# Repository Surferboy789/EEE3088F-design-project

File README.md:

# EEE3088F-design-project
Collaborative space for EEE3088F design project

Hi guys, try edit this file to make sure you have been added as a collaborator correctly. Thanks

Leoma edited
Matt testing git pull and push

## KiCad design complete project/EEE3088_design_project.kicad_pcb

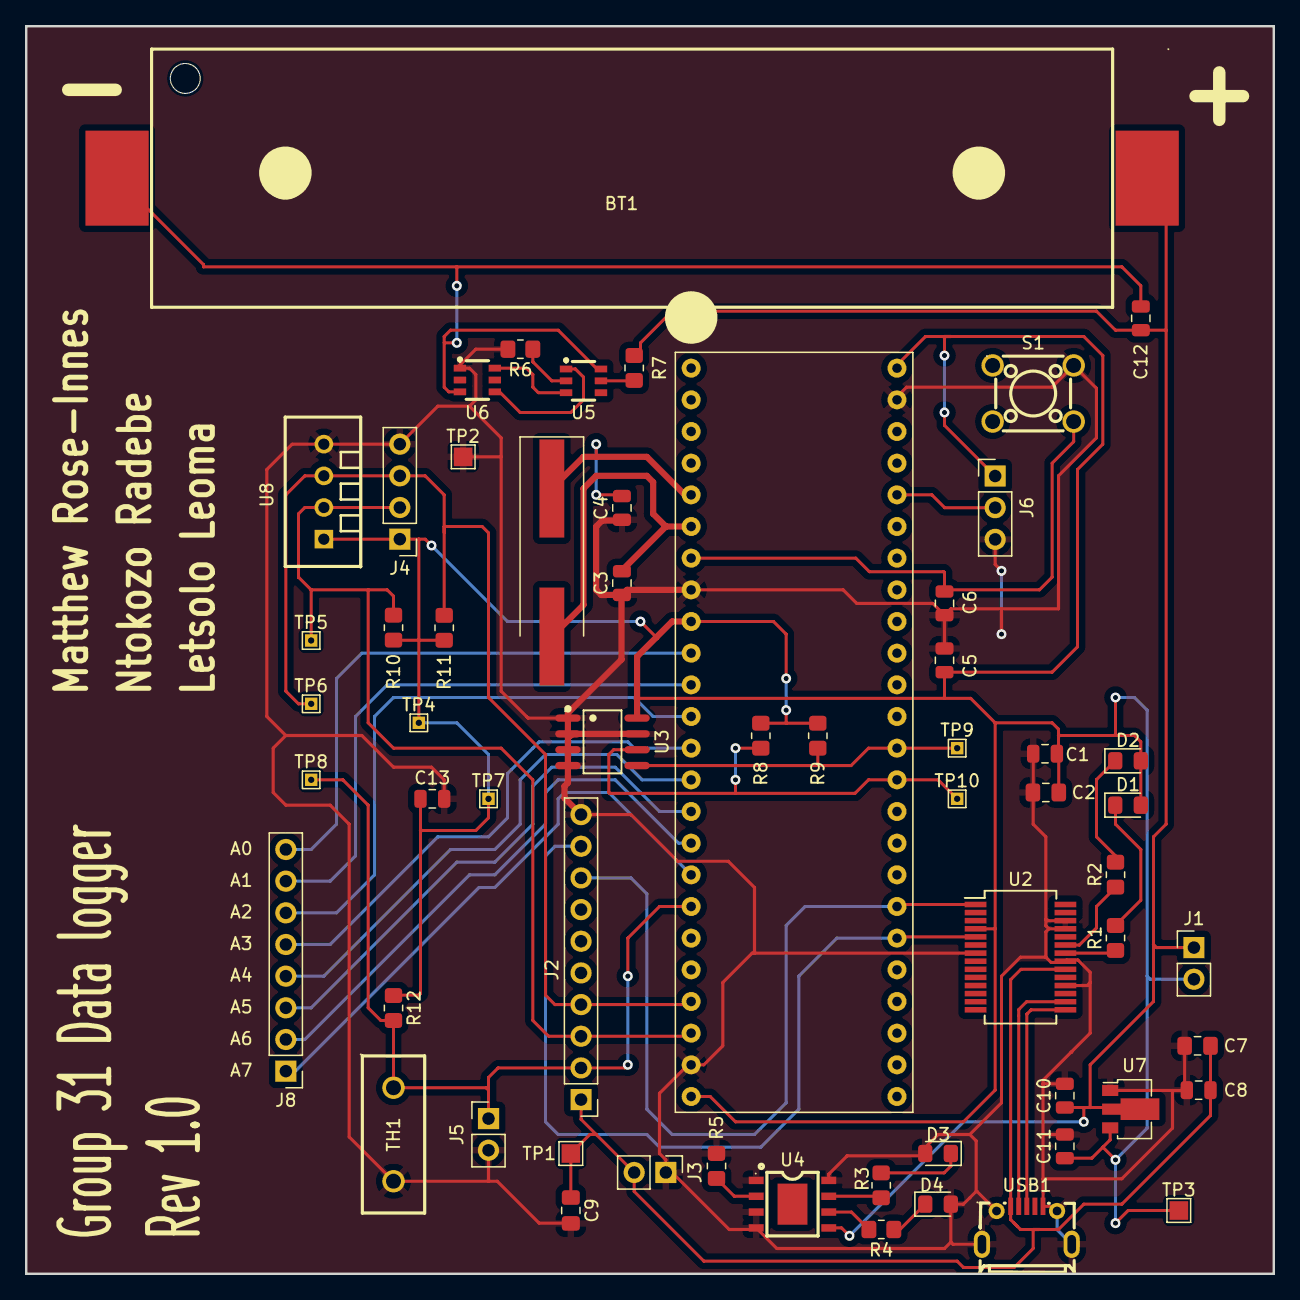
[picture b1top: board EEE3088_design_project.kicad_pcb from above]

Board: 2 copper layers, 100.1 x 100.1 mm, 59 parts (0 on the bottom side), 39 nets.

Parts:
BT1: Battery_Cell; BATTERY holder
C1, C12: 10nF; C_0805_2012Metric
C2: 1uF; C_0805_2012Metric_Pad1.18x1.45mm_HandSolder
C3, C4: 20pF; C_0805_2012Metric
C5, C6, C8: 100nF; C_0805_2012Metric
C7, C9: 10uF; C_0805_2012Metric_Pad1.18x1.45mm_HandSolder
C10, C11: 10uF; C_0805_2012Metric
C13: 100n; C_0805_2012Metric
D1, D2: LED; LED_0805_2012Metric_Pad1.15x1.40mm_HandSolder
D3: RED LED; LED_0805_2012Metric_Pad1.15x1.40mm_HandSolder
D4: GREEN LED; LED_0805_2012Metric_Pad1.15x1.40mm_HandSolder
J1, J3: Conn_01x02_Male; PinHeader_1x02_P2.54mm_Vertical
J2: Conn_01x10_Pin; PinHeader_1x10_P2.54mm_Vertical
J4: Conn_01x04_Pin; PinHeader_1x04_P2.54mm_Vertical
J5: Conn_01x02_Pin; PinHeader_1x02_P2.54mm_Vertical
J6: Conn_01x03_Pin; PinHeader_1x03_P2.54mm_Vertical
J7: Conn_02x24_Counter_Clockwise; STM32F051C6T6
J8: Conn_01x08_Pin; PinHeader_1x08_P2.54mm_Vertical
R1, R2: 330R; R_0805_2012Metric_Pad1.20x1.40mm_HandSolder
R3, R4: 1K; R_0805_2012Metric_Pad1.20x1.40mm_HandSolder
R5, R6: 1k; R_0805_2012Metric_Pad1.20x1.40mm_HandSolder
R7: 500; R_0805_2012Metric_Pad1.20x1.40mm_HandSolder
R8, R9: 4K7; R_0805_2012Metric_Pad1.20x1.40mm_HandSolder
R10, R11: 4.7k; R_0805_2012Metric_Pad1.20x1.40mm_HandSolder
R12: 5k; R_0805_2012Metric_Pad1.20x1.40mm_HandSolder
S1: C13828; SW-TH_4P-L6.0-W6.0-P4.50-LS6.5
TH1: Thermistor; RES-TH_L12.5-W5.0-P7.50-D0.7
TP1: TestPoint; TestPoint_Pad_1.5x1.5mm
TP2: GND; TestPoint_Pad_1.5x1.5mm
TP3: 3.3V; TestPoint_Pad_1.5x1.5mm
TP4: TestPoint; TestPoint_THTPad_1.0x1.0mm_Drill0.5mm
TP5: Temp SDA; TestPoint_THTPad_1.0x1.0mm_Drill0.5mm
TP6: Temp SLC; TestPoint_THTPad_1.0x1.0mm_Drill0.5mm
TP7: V3.3; TestPoint_THTPad_1.0x1.0mm_Drill0.5mm
TP8: Analog sens; TestPoint_THTPad_1.0x1.0mm_Drill0.5mm
TP9: Eprom SDA; TestPoint_THTPad_1.0x1.0mm_Drill0.5mm
TP10: Eprom SLC; TestPoint_THTPad_1.0x1.0mm_Drill0.5mm
U2: FT232RL; SSOP-28_5.3x10.2mm_P0.65mm
U3: AT24C256C-SSHL-T; SOIC-8_L4.9-W3.9-P1.27-LS6.0-BL
U4: TP4056; ESOP-8_L4.9-W3.9-P1.27-LS6.0-BL-EP
U5: DW01A-G; SOT-23
U6: FS8205A_C908265; SOT-23-6_L2.9-W1.6-P0.95-LS2.8-BR
U7: HT75xx-1-SOT89; SOT-89-3
U8: DHT22; SENSOR-TH_HAIGU_DHT22
USB1: MICROXNJ; MICRO-USB-SMD_MICROXNJ
Y1: 8MHz; Crystal_SMD_HC49-SD_HandSoldering

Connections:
5V: C7.2, C8.2, C9.1, J2.1, J3.2, TP1.1, U2.20 (VCC), USB1.1 (VBUS)
/Microcontroller Interface/D+: U2.15 (USBD+), USB1.3 (D+)
/Microcontroller Interface/D-: U2.16 (USBD-), USB1.2 (D-)
/Microcontroller Interface/Eprom_SDA: J7.36, R9.1, TP9.1, U3.5 (SDA)
/Microcontroller Interface/Eprom_SLC: J7.35, R8.1, TP10.1, U3.6 (SCL)
/Microcontroller Interface/NRST: C6.2, J7.7, S1.4
/Microcontroller Interface/RX: J2.9, J7.30, U2.5 (RXD)
/Microcontroller Interface/TX: J2.8, J7.31, U2.1 (TXD)
/Power managment/OC: U5.3 (OC), U6.6 (G1)
/Power managment/OD: U5.1 (OD), U6.4 (G2)
/Power managment/POS_terminal: BT1.1 (+), C10.1, C12.1, J1.1, R7.1, U4.5 (BAT), U7.2 (VIN)
Analog temp sensor: J2.2, J5.1, J7.18, R12.2, TH1.1, TP8.1
GND: C1.1, C2.1, C3.1, C4.1, C5.1, C6.1, C7.1, C8.1, C9.2, C10.2, C11.2, C13.2, D3.2 (A), D4.2 (A), J2.10, J3.1, J4.4, J5.2, J6.3, J7.8, J7.23, J7.47, R5.2, R6.2, S1.2, TH1.2, TP2.1, U2.7 (GND), U2.18 (GND), U2.21 (GND), U2.25 (AGND), U2.26 (TEST), U3.1 (A0), U3.2 (A1), U3.3 (A2), U3.4 (GND), U3.7 (WP), U4.1 (TEMP), U4.3 (GND), U4.4 (VCC), U4.8 (CE), U6.1 (S1), U7.1 (GND), U8.4 (GND), USB1.5 (GND), USB1.6 (SH1), USB1.7 (SH2), USB1.8 (SH3), USB1.9 (SH4)
unnamed: BT1.2 (-), C12.2, U5.6 (GND), U6.3 (S2)
unnamed: D1.1 (K), R1.2
unnamed: D2.1 (K), R2.2
unnamed: D3.1 (K), R3.1
unnamed: D4.1 (K), R4.1
unnamed: J6.2, J7.44
unnamed: C4.2, J7.5, Y1.1
unnamed: C3.2, J7.6, Y1.2
unnamed: R2.1, U2.23 (CBUS0)
unnamed: R1.1, U2.22 (CBUS1)
unnamed: R3.2, U4.7 (CHRG#)
unnamed: R5.1, U4.2 (PROG)
unnamed: R4.2, U4.6 (STDBY#)
unnamed: R6.1, U5.2 (CS)
unnamed: R7.2, U5.5 (VCC)
PA0: J7.10, J8.8
PA1: J7.11, J8.7
PA2: J7.12, J8.6
PA3: J7.13, J8.5
PA4: J7.14, J8.4
PA5: J7.15, J8.3
PA6: J7.16, J8.2
PA7: J7.17, J8.1
Temp_Sensor_SDA: J2.3, J4.2, J7.22, R10.2, TP5.1, U8.2 (SDA)
Temp_Sensor_SLC: J2.4, J4.3, J7.21, R11.2, TP6.1, U8.3 (SCK)
Vout3: C1.2, C2.2, C5.2, C11.1, C13.1, D1.2 (A), D2.2 (A), J1.2, J4.1, J6.1, J7.9, J7.24, J7.48, R8.2, R9.2, R10.1, R11.1, R12.1, TP3.1, TP4.1, TP7.1, U2.4 (VCCIO), U3.8 (VCC), U7.3 (VOUT), U8.1 (VDD)

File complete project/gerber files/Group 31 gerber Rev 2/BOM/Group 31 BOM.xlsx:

REFERENCE | VALUE | Extended Part | JLCPCB part no: | populate | Package | Price per unit | Total Price | Quantity
BT1 | Battery_Cell |  |  |  |  |  |  | 1
C9-C11 | 10uF | 0 | C15850 | Yes | .0805 | $0.0135 | $0.0405 | 3
C12 | 10nF | 0 | C57112 | Yes | .0603 | $0.0013 | $0.0013 | 1
D3 | RED LED | 0 | C2286 | Yes | LED_0603 | $0.0054 | $0.0054 | 1
D4 | GREEN LED | 0 | C2297 | Yes | .0805 | $0.0133 | $0.0133 | 1
U5 | DW01A-G | 1 | C61503 | Yes | SOT-23-6 | $0.1461 | $0.1461 | 1
J1, J3 | Conn_01x02_Male |  |  | no |  |  |  | 2
U6 | FS8205A | 1 | C908265 | yes | SOT-23-6 | $0.0552 | $0.0552 | 1
R3, R4, R5, R6 | 1K | 0 | C17414 | yes | 805 | 1E-3 | 4.0000000000000001E-3 | 3
7 | 500R | 0 | C17470 | yes | .0805 | 1.8E-3 | 1.8E-3 | 1
TP1, TP2 | TestPoint |  |  | no |  |  |  | 2
U7 | HT75xx-1-SOT89 | 0 | C14289 | yes | SOT-89-3 | $0.1315 | $0.1315 | 1
U4 | TP4056 | 0 | C16581 | yes | ESOP-8 | $0.2064 | $0.2064 | 1
C1 | 10nF | 0 | C49678 | yes | 805 | 4.5999999999999999E-3 | 4.5999999999999999E-3 | 1
C2 | 1uF | 0 | C28323 | yes | 805 | 8.6999999999999994E-3 | 8.6999999999999994E-3 | 1
C3, C4 | 20pF | 0 | C107145 | yes | 805 | 5.8999999999999999E-3 | 1.18E-2 | 2
C5, C6, C8 | 100nF | 0 | C49678 | yes | 805 | 4.5999999999999999E-3 | 1.38E-2 | 3
C7 | 10uF | 0 | C15850 | yes | 805 | 1.35E-2 | 1.35E-2 | 1
D1, D2 | LED | 0 | C2296 | yes | 805 | 1.1900000000000001E-2 | 3.9800000000000002E-2 | 2
J1 | USB_B_Micro | 1 | C404969 | yes | SMD | 3.3300000000000003E-2 | 3.0333000000000001 | 1
J2 | Conn_01x10_Pin |  |  | no |  |  |  | 1
R1, R2 | 330R | 0 | C17630 | yes | 805 | 1.6999999999999999E-3 | 3.3999999999999998E-3 | 2
SW1 | SW_Push | 1 | C13828 | yes | Through hole | 4.2500000000000003E-2 | 4.2500000000000003E-2 | 1
U1 | STM32 pin header |  |  | no |  |  |  | 1
U2 | FT232RL | 1 | C8690 | yes | SMD | 5.6292999999999997 | 8.6293000000000006 | 1
U3 | CAT24C256 | 0 | C6482 | yes | SOIC-8 | 0.53 | 0.53 | 1
R8, R9 | 4K7 | 0 | C17673 | yes | 805 | 1.6999999999999999E-3 | 3.3999999999999998E-3
J6 | Header |  |  | no
J8 | Header |  |  | no
Y1 | 8MHz | 0 | C12674 | yes | SMD | 8.6400000000000005E-2 | 8.6400000000000005E-2 | 1
C13 | 100nF | 0 | C49678 | yes | 805 | 4.5999999999999999E-3 | 4.5999999999999999E-3
R10, R11 | 4K7 | 0 | C17673 | yes | 805 | 1.6999999999999999E-3 | 3.3999999999999998E-3
J4 | Header |  |  | no
J5 | Header |  |  | no
TH1 | Thermistor | 1 | C190085 | yes | Through hole | $0.0353 | $0.0353
R12 | 5k | 0 | C784215 | yes | 805 | 2E-3 | 2E-3
U8 | DHT22 | 1 | C2880291 | yes | plugin | 1.4418 | 1.4418
 |  |  |  |  |  | Total cost | 13.878099999999998

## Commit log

2023-03-05 microcontroller files
2023-03-05 Assignment 2 microcontroller sub-module complete
2023-03-06 Create Power Management Submodule
2023-03-06 Create BOM
2023-03-13 assignment wk4 update
2023-03-14 Added Updated BOM
2023-03-14 added power managment
2023-03-20 added PCB files
2023-03-20 Changed directory of final project
2023-03-20 Latest update of PCB
2023-03-21 added BOM
2023-03-21 Updated Sensor Submodule BOM
    Updated BOM
2023-03-21 added gerber
2023-04-03 latest copy of PCB
2023-04-13 corrected group details
2023-04-13 update Justins comments
2023-04-25 Add files via upload
    Schematic of the sensory circuit
